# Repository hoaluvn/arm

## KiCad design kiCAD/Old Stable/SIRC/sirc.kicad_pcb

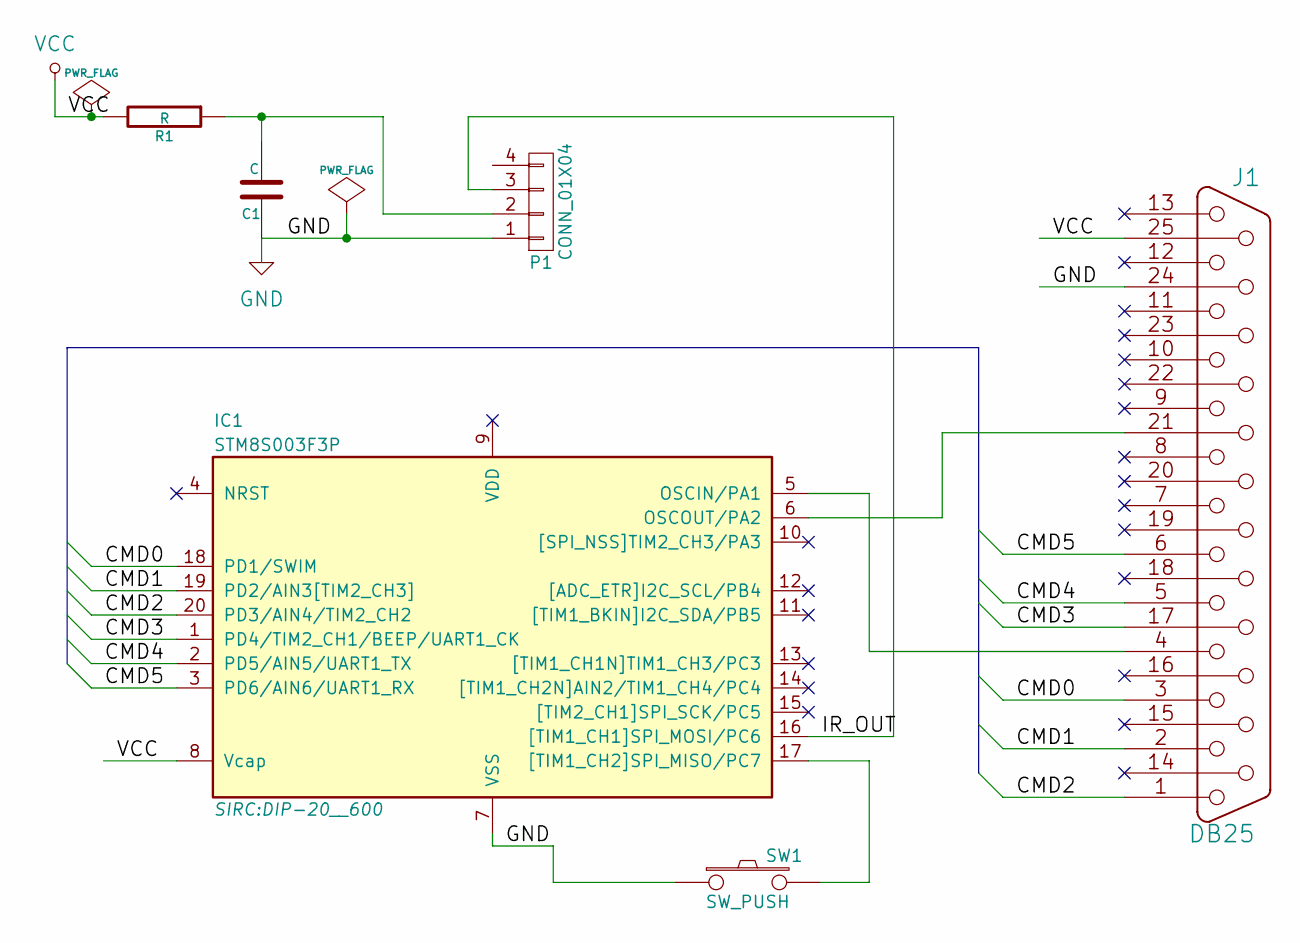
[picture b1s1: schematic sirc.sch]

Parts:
C1: C; C1-1
IC1: STM8S003F3P; DIP-20__600
J1: DB25; DB25FC
P1: CONN_01X04; Pin_Header_Straight_1x04
R1: R; R3
SW1: SW_PUSH

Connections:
/CMD0: IC1.18 (PD1/SWIM), J1.3
/CMD1: IC1.19 (PD2/AIN3[TIM2_CH3]), J1.2
/CMD2: IC1.20 (PD3/AIN4/TIM2_CH2), J1.1
/CMD3: IC1.1 (PD4/TIM2_CH1/BEEP/UART1_CK), J1.17
/CMD4: IC1.2 (PD5/AIN5/UART1_TX), J1.5
/CMD5: IC1.3 (PD6/AIN6/UART1_RX), J1.6
/IR_OUT: IC1.16 ([TIM1_CH1]SPI_MOSI/PC6), P1.3
GND: C1.1, IC1.7 (VSS), J1.24, P1.1, SW1.1
unnamed: IC1.5 (OSCIN/PA1), J1.4
unnamed: IC1.6 (OSCOUT/PA2), J1.21
unnamed: IC1.17 ([TIM1_CH2]SPI_MISO/PC7), SW1.2
unnamed: C1.2, P1.2, R1.1
VCC: IC1.8 (Vcap), J1.25, R1.2

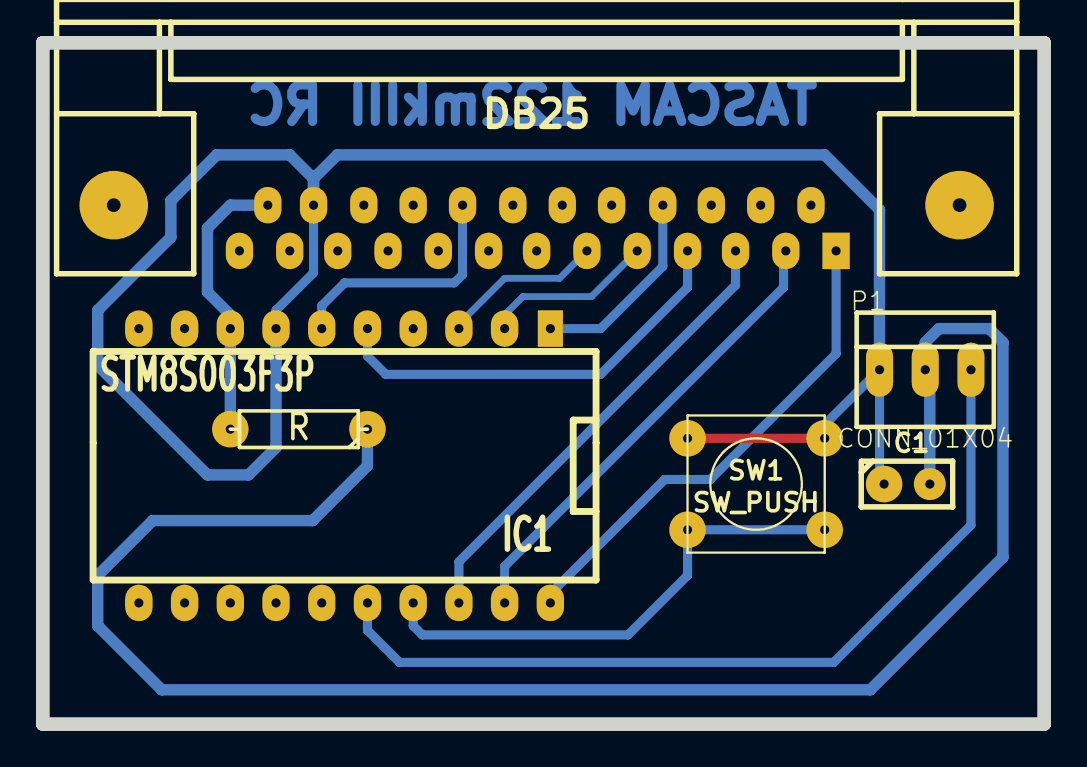
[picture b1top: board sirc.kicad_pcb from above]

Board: 2 copper layers, 55.6 x 37.8 mm, 6 parts (0 on the bottom side), 13 nets.

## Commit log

2015-02-05 add stm32 stand peripheral lib
2015-02-08 add tilen, libopencm3-example
2015-02-09 add README
2015-02-09 add nRF24L01
2015-02-10 some update
2015-02-14 add nrf24l01 prj
2015-02-14 add button
2015-03-23 Pulled down update to submodule lib/tilen
2015-03-25 sync
2015-03-31 add STM32Cube
2015-03-31 add new HAL template for F1
2015-03-31 small update
2015-03-31 update STM32-Template
2015-04-01 new stm32f103c6t8 gpio toggle
2015-04-01 compile clean
2015-04-02 add binary
2015-04-03 add hex and bin format
2015-04-06 F1 gpio CooCox prj
2015-04-06 FIX LED pin: GPIOC.13
2015-04-07 add hex, bin
2015-04-07 fix Clock init
2015-04-08 fix Systick IRQ
2015-04-09 clean up
2015-04-10 update makefile
2015-04-10 clean .swp files
2015-04-10 add tags
2015-04-10 add an3174 Infra receiver prj
2015-04-12 clean build for IR prj
2015-04-22 add STM8 std library
2015-04-22 update IR
2015-04-23 add STM8S GPIO Toggle
2015-05-09 update gpio-togle prj
2015-05-09 add SIRC for stm8s prj
2015-05-09 update Infra prj stm32
2015-05-10 Add kiCAD projects
2015-05-14 Seperate old & new version
2015-05-14 Complete first version. Next commit will change schematic for better routing
2015-05-15 improve timing, avoid hang
2015-05-18 Add submodule kiCAD template
2015-05-18 Revision 2, fix DB25 female -> male
2015-05-19 add DHT11 prj
